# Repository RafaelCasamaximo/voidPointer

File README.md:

# ⌨️ voidPointer

The **voidPointer** is a 65% fully wireless keyboard, born from a love for the classic aesthetics of the [Discipline V2](https://github.com/coseyfannitutti/discipline), but redesigned from the ground up for a modern, cable-free setup.

It's a project that celebrates the beauty of exposed through-hole components and the freedom of Bluetooth connectivity with ZMK.

This is a WIP, so continue carefully. Also, I have changed the layout to only be ANSI because it creates various errors on KiCad with holes overlaping vias. Changing it back to ISO would require you to insert the missing switches and holes, and also routing these pads into the existing rows and columns.

---

## ✨ Main Features

- **100% Wireless:** Bluetooth Low Energy (BLE) connectivity with ZMK firmware.
- **Battery Efficiency:** Designed for months of use on a single charge (no LEDs).
- **nRF52840 Microcontroller:** Uses the `nice!nano v2` (or a compatible module) as its brain.
- **65% Layout:** A compact and popular layout, based on the Discipline.
- **THT (Through-Hole) Aesthetics:** Maintains the iconic design with visible `1N4148` diodes.
- **Hotswap (Optional):** The PCB is designed for soldering, but can be easily converted to hotswap using Mill-Max sockets (`7305` or `0305`).
- **Robust Firmware:** Runs the powerful [ZMK Firmware](https://zmk.dev/), enabling layers, macros, and multi-device support.

## 📖 About the Project

This project is a _remix_ and a tribute to the incredible work of **coseyfannitutti**. While the original Discipline is a masterpiece of wired design, the `voidPointer` adapts that philosophy to the wireless world.

The name `voidPointer` is a play on the C language, referencing a generic pointer that can point to "anything" — or, in this case, a pointer to nothing (void), celebrating the absence of wires.

## 🛠️ Technical Details and Components (BOM)

This is not an exhaustive list, but it covers the main components.

| Component                 | Quantity | Specification (Example)                                                                    |
| :------------------------ | :------- | :----------------------------------------------------------------------------------------- |
| **Custom PCB**            | 1        | `voidPointer` (Gerber files in the JLCPCB-supported format in the `/production` directory) |
| **Microcontroller**       | 1        | `nice!nano` v2 or `SuperMini nRF52840`                                                     |
| **Sockets for Micro**     | 2        | Male/Female Pin Headers (2x12) or Mill-Max Sockets                                         |
| **Diodes**                | ~68      | `1N4148` (Through-Hole THT)                                                                |
| **Power Switch**          | 1        | Slider Switch (ex: SS-12D00)                                                               |
| **Battery Connector**     | 1        | `JST-PH` 2-Pin (Horizontal)                                                                |
| **Capacitor (Filter)**    | 1        | `100nF` (0.1µF) - THT Ceramic (Ex: 104) or SMD (0805)                                      |
| **Capacitor (Reservoir)** | 1        | `10µF` - THT Ceramic or SMD (1206)                                                         |
| **Battery**               | 1        | LiPo (ex: 1200-2000mAh) with JST-PH connector                                              |
| **Switches**              | ~68      | MX-Style (3 or 5 pin)                                                                      |
| **Hotswap Sockets**       | ~136     | (Optional) Mill-Max `7305` or `0305`                                                       |
| **Stabilizers**           | 4        | PCB Mount (2u x3, 6.25u x1)                                                                |
| **Case Hardware**         | ~12      | M2 Screws and Standoffs                                                                    |

---

## ⚡ ZMK Firmware

This keyboard is designed for the [ZMK Firmware](https://zmk.dev/).

### My Config Repository

The firmware files (keymap, overlay, and config) for this project are not in this repository. They live in a separate repository, as is the ZMK standard.

➡️ **You can find my ZMK configuration here: [Config Repository](https://github.com/RafaelCasamaximo/VoidPointerFirmwareConfig)**

### How to Flash the Firmware

1.  Download the latest `.uf2` file from my config repository (in the "Actions" tab).
2.  Connect the microcontroller to the computer via USB.
3.  Press the **reset button** **twice quickly** (On the current version, this must be done by shorting the GND and RST pins on the micro).
4.  A "pen drive" (mass storage device) named `NICENANO` (or similar) will appear on your computer.
5.  **Drag and drop** the `.uf2` file onto this "pen drive".
6.  The device will automatically reboot with the new firmware.

---

## 🏗️ Assembly

1.  **Fabricate the PCB:** Upload the ZIP file from the `/production` directory to a PCB manufacturer (like JLCPCB, PCBWay, etc.).
2.  **PCB Assembly:**
    - **Soldering Order (IMPORTANT):** Solder components from the lowest to the highest profile.
    - 1. Diodes (Be careful with orientation! The black band must match the marking on the PCB).
    - 2. Capacitors, Power Switch, JST Connector.
    - 3. (Optional) Mill-Max Hotswap Sockets (Be patient!).
    - 4. Microcontroller Sockets.
    - 5. Install the Stabilizers.
3.  **Final Assembly:**
    - Fit the plate.
    - Insert the switches (if hotswap) or solder them (if solder).
    - Assemble the case sandwich with the screws and standoffs.
    - Connect the battery.
    - Fit the microcontroller into its sockets.
    - Put on the keycaps.

## Acknowledgements

- This project is a direct derivative of the **Discipline** and owes all its credit to **[coseyfannitutti](https://github.com/coseyfannitutti)**.
- To the entire **ZMK Firmware** team and community.

## License

Creative Commons Attribution-NonCommercial 4.0 International License

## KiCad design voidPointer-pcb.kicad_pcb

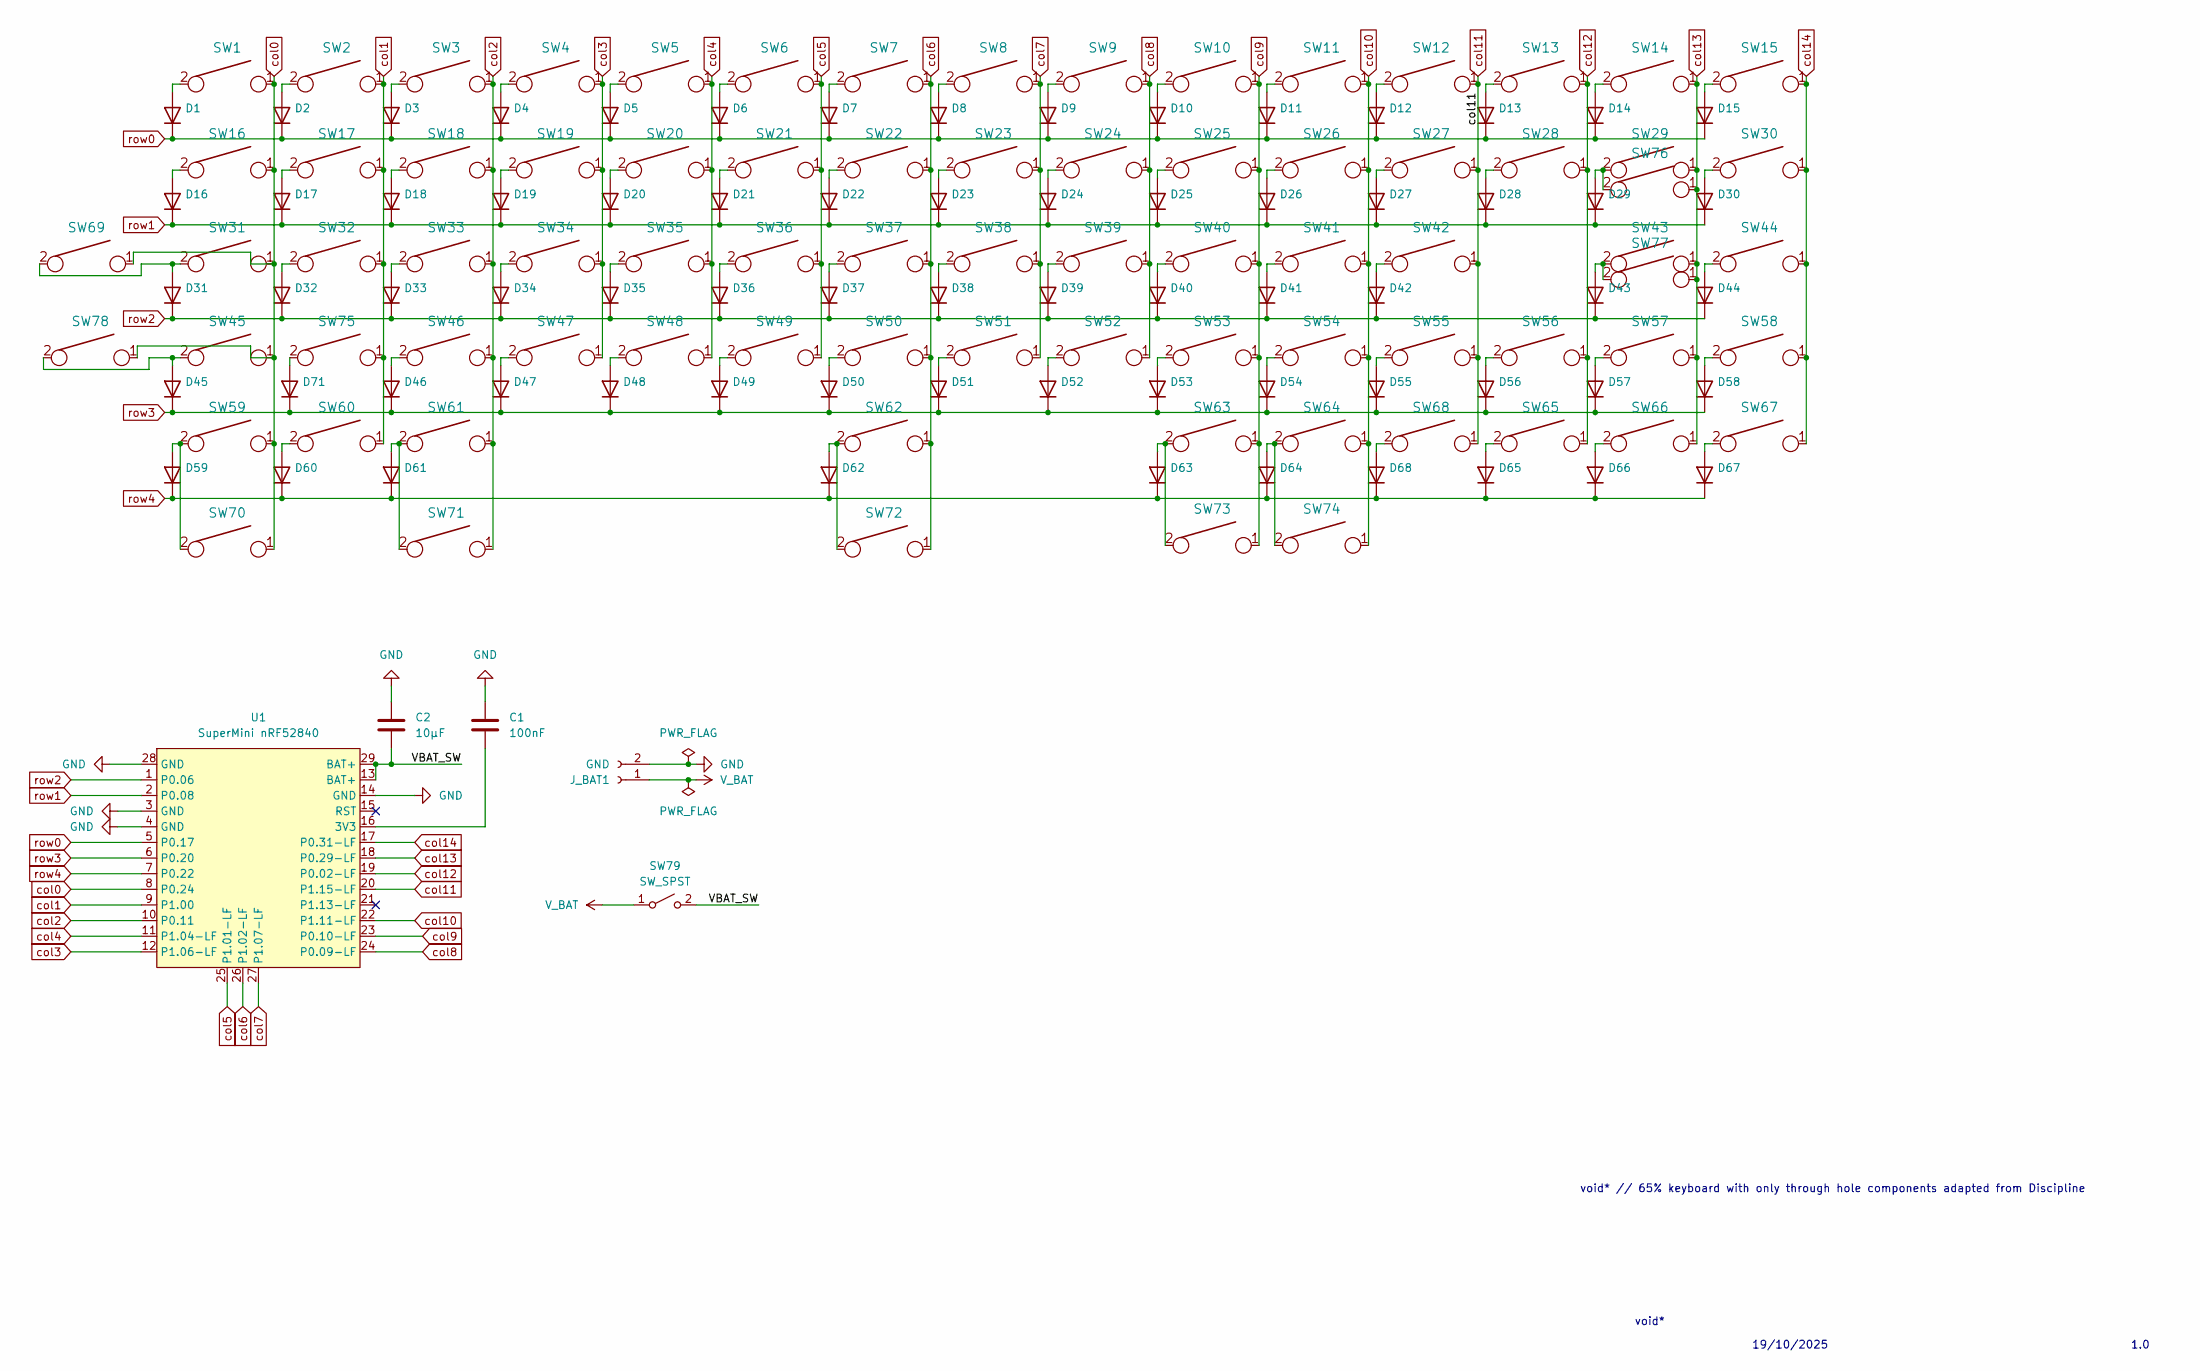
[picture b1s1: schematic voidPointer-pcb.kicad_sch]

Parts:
C1: 100nF; C_Rect_L11.5mm_W5.2mm_P10.00mm_MKT
C2: 10µF; C_Disc_D4.7mm_W2.5mm_P5.00mm
D1, D2, D3, D4, D5, D6, D7, D8, D9, D10, D11, D12, D13, D14, D15, D16, D17, D18, D19, D20, D21, D22, D23, D24, D25, D26, D27, D28, D29, D30, D31, D32, D33, D34, D35, D36, D37, D38, D39, D40, D41, D42, D43, D44, D45, D46, D47, D48, D49, D50, D51, D52, D53, D54, D55, D56, D57, D58, D59, D60, D61, D62, D63, D64, D65, D66, D67, D68, D71: D_DO-35_SOD27_P5.08mm_Horizontal
J_BAT1: GND; JST_PH_S2B-PH-K_1x02_P2.00mm_Horizontal
SW1, SW2, SW3, SW4, SW5, SW6, SW7, SW8, SW9, SW10, SW11, SW12, SW13, SW15, SW17, SW18, SW19, SW20, SW21, SW22, SW23, SW24, SW25, SW26, SW27, SW28, SW30, SW32, SW33, SW34, SW35, SW36, SW37, SW38, SW39, SW40, SW41, SW42, SW44, SW46, SW47, SW48, SW49, SW50, SW51, SW52, SW53, SW54, SW55, SW57, SW58, SW62, SW65, SW66, SW67, SW68, SW72, SW75, SW77: KEYSW; SW_Cherry_MX1A_1.00u_PCB-NOSCREEN
SW14: KEYSW; SW_Cherry_MX1A_2.00u_PCBNOSCREEN
SW16, SW29, SW70, SW71, SW73, SW74: KEYSW; SW_Cherry_MX1A_1.50u_PCBNOSCREEN
SW31, SW56: KEYSW; SW_Cherry_MX1A_1.75u_PCBNOSCREEN
SW43, SW45: KEYSW; SW_Cherry_MX1A_2.25u_PCBNOSCREEN
SW59, SW60, SW61, SW63, SW64, SW69, SW78: KEYSW; SW_Cherry_MX1A_1.25u_PCBNOSCREEN
SW76: KEYSW; SW_Cherry_MX1A_ISOEnter_PCB_ReversedStabilizer
SW79: SW_SPST; 1P2T_SS-12D00_CNK
U1: SuperMini nRF52840; SuperMini_nRF52840_AH_USBup

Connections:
/VBAT_SW: C2.2, SW79.2 (B), U1.13 (BAT+), U1.29 (BAT+)
GND: C1.2, C2.1, J_BAT1.2, U1.3 (GND), U1.4 (GND), U1.14 (GND), U1.28 (GND)
unnamed: D1.2 (A), SW1.2
unnamed: D2.2 (A), SW2.2
unnamed: D3.2 (A), SW3.2
unnamed: D4.2 (A), SW4.2
unnamed: D5.2 (A), SW5.2
unnamed: D6.2 (A), SW6.2
unnamed: D7.2 (A), SW7.2
unnamed: D8.2 (A), SW8.2
unnamed: D9.2 (A), SW9.2
unnamed: D10.2 (A), SW10.2
unnamed: D11.2 (A), SW11.2
unnamed: D12.2 (A), SW12.2
unnamed: D13.2 (A), SW13.2
unnamed: D14.2 (A), SW14.2
unnamed: D15.2 (A), SW15.2
unnamed: D16.2 (A), SW16.2
unnamed: D17.2 (A), SW17.2
unnamed: D18.2 (A), SW18.2
unnamed: D19.2 (A), SW19.2
unnamed: D20.2 (A), SW20.2
unnamed: D21.2 (A), SW21.2
unnamed: D22.2 (A), SW22.2
unnamed: D23.2 (A), SW23.2
unnamed: D24.2 (A), SW24.2
unnamed: D25.2 (A), SW25.2
unnamed: D26.2 (A), SW26.2
unnamed: D27.2 (A), SW27.2
unnamed: D28.2 (A), SW28.2
unnamed: D29.2 (A), SW29.2, SW76.2
unnamed: D30.2 (A), SW30.2
unnamed: D31.2 (A), SW31.2, SW69.2
unnamed: D32.2 (A), SW32.2
unnamed: D33.2 (A), SW33.2
unnamed: D34.2 (A), SW34.2
unnamed: D35.2 (A), SW35.2
unnamed: D36.2 (A), SW36.2
unnamed: D37.2 (A), SW37.2
unnamed: D38.2 (A), SW38.2
unnamed: D39.2 (A), SW39.2
unnamed: D40.2 (A), SW40.2
unnamed: D41.2 (A), SW41.2
unnamed: D42.2 (A), SW42.2
unnamed: D43.2 (A), SW43.2, SW77.2
unnamed: D44.2 (A), SW44.2
unnamed: D45.2 (A), SW45.2, SW78.2
unnamed: D46.2 (A), SW46.2
unnamed: D47.2 (A), SW47.2
unnamed: D48.2 (A), SW48.2
unnamed: D49.2 (A), SW49.2
unnamed: D50.2 (A), SW50.2
unnamed: D51.2 (A), SW51.2
unnamed: D52.2 (A), SW52.2
unnamed: D53.2 (A), SW53.2
unnamed: D54.2 (A), SW54.2
unnamed: D55.2 (A), SW55.2
unnamed: D56.2 (A), SW56.2
unnamed: D57.2 (A), SW57.2
unnamed: D58.2 (A), SW58.2
unnamed: D59.2 (A), SW59.2, SW70.2
unnamed: D60.2 (A), SW60.2
unnamed: D61.2 (A), SW61.2, SW71.2
unnamed: D62.2 (A), SW62.2, SW72.2
unnamed: D63.2 (A), SW63.2, SW73.2
unnamed: D64.2 (A), SW64.2, SW74.2
unnamed: D65.2 (A), SW65.2
unnamed: D66.2 (A), SW66.2
unnamed: D67.2 (A), SW67.2
unnamed: D68.2 (A), SW68.2
unnamed: D71.2 (A), SW75.2
unnamed: C1.1, U1.16 (3V3)
V_BAT: J_BAT1.1, SW79.1 (A)
col0: SW1.1, SW16.1, SW31.1, SW45.1, SW59.1, SW69.1, SW70.1, SW78.1, U1.8 (P0.24)
col1: SW2.1, SW17.1, SW32.1, SW60.1, SW75.1, U1.9 (P1.00)
col2: SW3.1, SW18.1, SW33.1, SW46.1, SW61.1, SW71.1, U1.10 (P0.11)
col3: SW4.1, SW19.1, SW34.1, SW47.1, U1.12 (P1.06-LF)
col4: SW5.1, SW20.1, SW35.1, SW48.1, U1.11 (P1.04-LF)
col5: SW6.1, SW21.1, SW36.1, SW49.1, U1.25 (P1.01-LF)
col6: SW7.1, SW22.1, SW37.1, SW50.1, SW62.1, SW72.1, U1.26 (P1.02-LF)
col7: SW8.1, SW23.1, SW38.1, SW51.1, U1.27 (P1.07-LF)
col8: SW9.1, SW24.1, SW39.1, SW52.1, U1.24 (P0.09-LF)
col9: SW10.1, SW25.1, SW40.1, SW53.1, SW63.1, SW73.1, U1.23 (P0.10-LF)
col10: SW11.1, SW26.1, SW41.1, SW54.1, SW64.1, SW74.1, U1.22 (P1.11-LF)
col11: SW12.1, SW27.1, SW42.1, SW55.1, SW68.1, U1.20 (P1.15-LF)
col12: SW13.1, SW28.1, SW56.1, SW65.1, U1.19 (P0.02-LF)
col13: SW14.1, SW29.1, SW43.1, SW57.1, SW66.1, SW76.1, SW77.1, U1.18 (P0.29-LF)
col14: SW15.1, SW30.1, SW44.1, SW58.1, SW67.1, U1.17 (P0.31-LF)
row0: D1.1 (K), D2.1 (K), D3.1 (K), D4.1 (K), D5.1 (K), D6.1 (K), D7.1 (K), D8.1 (K), D9.1 (K), D10.1 (K), D11.1 (K), D12.1 (K), D13.1 (K), D14.1 (K), D15.1 (K), U1.5 (P0.17)
row1: D16.1 (K), D17.1 (K), D18.1 (K), D19.1 (K), D20.1 (K), D21.1 (K), D22.1 (K), D23.1 (K), D24.1 (K), D25.1 (K), D26.1 (K), D27.1 (K), D28.1 (K), D29.1 (K), D30.1 (K), U1.2 (P0.08)
row2: D31.1 (K), D32.1 (K), D33.1 (K), D34.1 (K), D35.1 (K), D36.1 (K), D37.1 (K), D38.1 (K), D39.1 (K), D40.1 (K), D41.1 (K), D42.1 (K), D43.1 (K), D44.1 (K), U1.1 (P0.06)
row3: D45.1 (K), D46.1 (K), D47.1 (K), D48.1 (K), D49.1 (K), D50.1 (K), D51.1 (K), D52.1 (K), D53.1 (K), D54.1 (K), D55.1 (K), D56.1 (K), D57.1 (K), D58.1 (K), D71.1 (K), U1.6 (P0.20)
row4: D59.1 (K), D60.1 (K), D61.1 (K), D62.1 (K), D63.1 (K), D64.1 (K), D65.1 (K), D66.1 (K), D67.1 (K), D68.1 (K), U1.7 (P0.22)

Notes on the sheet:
1.0
void*
void* // 65% keyboard with only through hole components adapted from Discipline
19/10/2025

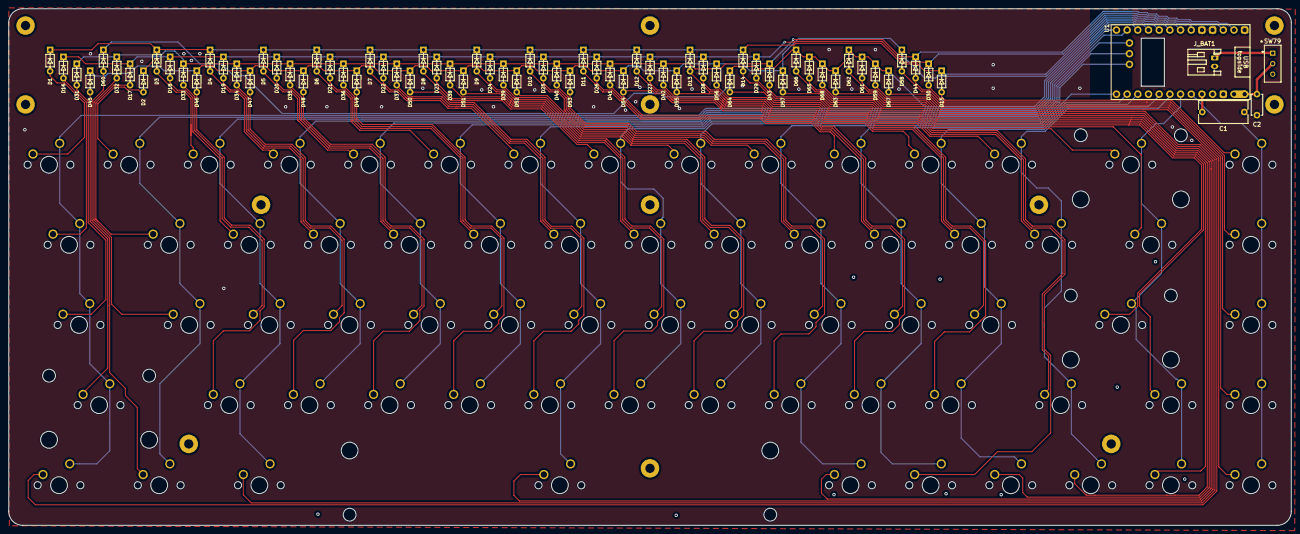
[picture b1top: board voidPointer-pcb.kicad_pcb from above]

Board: 2 copper layers, 304.9 x 122.8 mm, 141 parts (0 on the bottom side), 92 nets.

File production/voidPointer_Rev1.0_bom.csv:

Designator,Footprint,Quantity,Value,LCSC Part #
C1,C_Rect_L11.5mm_W5.2mm_P10.00mm_MKT,1,100nF,
C2,C_Disc_D4.7mm_W2.5mm_P5.00mm,1,10µF,
"D1, D10, D11, D12, D13, D14, D15, D16, D17, D18, D19, D2, D20, D21, D22, D23, D24, D25, D26, D27, D28, D29, D3, D30, D31, D32, D33, D34, D35, D36, D37, D38, D39, D4, D40, D41, D42, D43, D44, D45, D46, D47, D48, D49, D5, D50, D51, D52, D53, D54, D55, D56, D57, D58, D59, D6, D60, D61, D62, D63, D64, D65, D66, D67, D68, D7, D8, D9",D_DO-35_SOD27_P5.08mm_Horizontal,68,~,
J_BAT1,JST_PH_S2B-PH-K_1x02_P2.00mm_Horizontal,1,GND,
"SW1, SW10, SW11, SW12, SW13, SW15, SW17, SW18, SW19, SW2, SW20, SW21, SW22, SW23, SW24, SW25, SW26, SW27, SW28, SW3, SW30, SW32, SW33, SW34, SW35, SW36, SW37, SW38, SW39, SW4, SW40, SW41, SW42, SW44, SW46, SW47, SW48, SW49, SW5, SW50, SW51, SW52, SW53, SW54, SW55, SW57, SW58, SW6, SW62, SW65, SW66, SW67, SW68, SW7, SW8, SW9",SW_Cherry_MX1A_1.00u_PCB-NOSCREEN,56,KEYSW,
SW14,SW_Cherry_MX1A_2.00u_PCBNOSCREEN,1,KEYSW,
"SW16, SW29",SW_Cherry_MX1A_1.50u_PCBNOSCREEN,2,KEYSW,
"SW31, SW56",SW_Cherry_MX1A_1.75u_PCBNOSCREEN,2,KEYSW,
"SW43, SW45",SW_Cherry_MX1A_2.25u_PCBNOSCREEN,2,KEYSW,
"SW59, SW60, SW61, SW63, SW64",SW_Cherry_MX1A_1.25u_PCBNOSCREEN,5,KEYSW,
SW79,1P2T_SS-12D00_CNK,1,SW_SPST,

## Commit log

2025-11-03 Versão base com nice
2025-11-03 Esqueci de salvar rs
2025-11-08 Removing keys for the ISO layout
2025-11-08 Finishing JLCPCB support and implementing decoupling capacitors
2025-11-11 Adding GND plane to back layer and rerouting
2025-11-16 Removing files that are not usefull
2025-11-16 Renaming files
2025-11-16 Renaming project revision and title
2025-11-16 Refactoring the README
2025-12-23 Fixing small issues on the project and updating readme
